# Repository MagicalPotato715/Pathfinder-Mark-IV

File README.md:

# Pathfinder-Mark-IV
**IMPORTANT FOR REVIEWERS**: 
 - 1. The PCB price *really* is at the lowest it could possibly be, it's not possible to lower the price OR try to find a cheaper fab, I already thoroughly went through this with the reviewer @technical_ and he said that it's acceptable.
 - 2. The BOM is already optimized, and NO the parts on Aliexpress and Digikey cannot be sourced from LCSC (technically, LCSC does *sell* the terminal block, but the one seller's out of stock and has been for a while).
 - 3. This is NOT similar to Mk-III in ANY way aside from the fact that it's a hexapod. (if you reviewed it you'd know that) The entire system is completely different. Mk-III was a Nucleo Shield that used a 7.4v lipo battery connected to 3 buck converters directly connected to passives, that was basically it. However, Mk-IV is an on-board, Teensy, with a 6.6v Li-Fe Battery connected to a terminal-rocker switch system, with a back side I2C expander with 8 Tof Sensors.

If you don't believe me, ask @technical_, @NotARoomba, or @Tanook

What: Mark IV will be the fourth generation of my hexapod line: Pathfinder (not to be confused with the Hack Club YSWS). Mark IV will feature major consistency improvements to Mark III (mainly just not featuring buck converters). Additionally, Mark IV has an I2C expander connected to 8 ToF sensors that should allow the finished robot to have some form of autonomous movement.

Note: This project primarily focuses on the PCB of the Mark IV, as the body has already been printed, so it's a secondary focus (however, design tweaks may still be made to it).

Why: I began Pathfinder a year ago after my physics teacher encouraged me to join my school's science fair. I had always had an idea for a spider robot that I kept at the back of my mind, but this pushed me to bring it to life. Over the next few weeks, I poured hours every day into learning more about mechanical and electrical engineering. I also sought mentorship from the UC Berkeley Engineering Department and got connected with a Mech E & EECS graduate student. Mark I of Pathfinder, a simple prototype/proof of concept, was churned out after 2 weeks, just in time for my district's science fair to win me 2nd place. Mark II was developed a few weeks later for the regional science fair, and it featured my very first PCB a simple wire connector that I created using Onboard. Mark III was developed in the months after the science fair. I attempted to create a Hexpod orders of magnitude larger, with a system heavily centered on the PCB (I developed this PCB with Highway). However, when I finally got the PCB, soldered all of the components, and plugged it in, the core of the design: one of 3 buck converters to take 15 amps of power from the 7.4v battery to the 18 servo motors, blew up; ending Mark III. I developed Mark IV to continue on and actualize Pathfinder.

3D Model (Chassis):

3D Model (PCB in Kicad):

PCB Layout:

F. Cu

In1. Cu

In2. Cu

B. Cu

PCB Schematic:

|Name                         |Amount|Unit Cost|Unit Size|Total |FIELD6                                                                                                                                                                                                                                                                                                                                                                                                                                                                                                                                                                                                                                                                                                                                                                                                                                                                    |
|-----------------------------|------|---------|---------|------|--------------------------------------------------------------------------------------------------------------------------------------------------------------------------------------------------------------------------------------------------------------------------------------------------------------------------------------------------------------------------------------------------------------------------------------------------------------------------------------------------------------------------------------------------------------------------------------------------------------------------------------------------------------------------------------------------------------------------------------------------------------------------------------------------------------------------------------------------------------------------|
|3.3v Zener Diode             |1     |0.74     |20       |0.74  |https://www.lcsc.com/product-detail/C7441074.html?s_z=n_1N4728A                                                                                                                                                                                                                                                                                                                                                                                                                                                                                                                                                                                                                                                                                                                                                                                                           |
|SMD Capacitor 10uf 0805      |2     |0.2      |20       |0.2   |https://www.lcsc.com/product-detail/C15850.html?s_z=n_SMD%2520Capacitor%25200805%252010uf                                                                                                                                                                                                                                                                                                                                                                                                                                                                                                                                                                                                                                                                                                                                                                                 |
|Header 1x3 M                 |18    |0.81     |20       |0.81  |https://www.lcsc.com/product-detail/C2937625.html?s_z=n_2.54mm%2520header                                                                                                                                                                                                                                                                                                                                                                                                                                                                                                                                                                                                                                                                                                                                                                                                 |
|Header 1x5 F                 |9     |0.58     |20       |0.58  |https://www.lcsc.com/product-detail/C492404.html?s_z=n_2.54mm                                                                                                                                                                                                                                                                                                                                                                                                                                                                                                                                                                                                                                                                                                                                                                                                             |
|SMD LED                      |20    |0.48     |50       |0.48  |https://www.lcsc.com/product-detail/C25170728.html                                                                                                                                                                                                                                                                                                                                                                                                                                                                                                                                                                                                                                                                                                                                                                                                                        |
|SMD Resistor 510ohm 0805     |19    |0.43     |50       |0.43  |https://www.lcsc.com/product-detail/C2828857.html?s_z=n_0805%2520LED                                                                                                                                                                                                                                                                                                                                                                                                                                                                                                                                                                                                                                                                                                                                                                                                      |
|Servo Motors                 |6     |35.26    |4        |70.52 |https://www.aliexpress.us/item/3256806709778108.html?spm=a2g0o.productlist.0.0.6ab56e340EHKOL&mp=1&pdp_npi=5%40dis%21USD%21USD%20130.38%21USD%2036.58%21%21USD%2036.58%21%21%21%402101062a17638804388948845ec99e%2112000038822514200%21ct%21US%216187826129%21%215%210&_gl=1*cljtcb*_gcl_aw*R0NMLjE3NjM4ODA2ODUuQ2p3S0NBaUEyNFhKQmhCWEVpd0FYRWxPM3liRHZJN1I1VnFod2RBbzJuRGJ3RkJwVWkxX3hRbkJBY2NBVHdfak5hWElKU20wNVJjNTJCb0NjTndRQXZEX0J3RQ..*_gcl_dc*R0NMLjE3NjM4ODA2ODUuQ2p3S0NBaUEyNFhKQmhCWEVpd0FYRWxPM3liRHZJN1I1VnFod2RBbzJuRGJ3RkJwVWkxX3hRbkJBY2NBVHdfak5hWElKU20wNVJjNTJCb0NjTndRQXZEX0J3RQ..*_gcl_au*MTUyNzUyMDgzOS4xNzU3ODgxNTQ1*_ga*MjEzNTUyNTk1My4xNzYzODc4NzU4*_ga_VED1YSGNC7*czE3NjM4Nzg3NTckbzEkZzEkdDE3NjM4ODA5MzQkajYwJGwwJGgw&gatewayAdapt=glo2usa                                                                                                      |
|Li-Fe Battery 6.6v 3000mah   |2     |19.32    |1        |38.64 |https://www.aliexpress.us/item/3256807464251198.html?src=google&pdp_npi=4%40dis%21USD%2111.90%218.33%21%21%21%21%21%40%2112000041655129505%21ppc%21%21%21&src=google&albch=shopping&acnt=231-612-1468&isdl=y&slnk=&plac=&mtctp=&albbt=Google_7_shopping&aff_platform=google&aff_short_key=_oFgTQeV&gclsrc=aw.ds&albagn=888888&ds_e_adid=&ds_e_matchtype=&ds_e_device=c&ds_e_network=x&ds_e_product_group_id=&ds_e_product_id=en3256807464251198&ds_e_product_merchant_id=101200748&ds_e_product_country=US&ds_e_product_language=en&ds_e_product_channel=online&ds_e_product_store_id=&ds_url_v=2&albcp=22977867118&albag=&isSmbAutoCall=false&needSmbHouyi=false&gad_source=1&gad_campaignid=22973747411&gbraid=0AAAABBR8kP1DsTtj-qFVjDN4WDyziy5WL&gclid=CjwKCAiA24XJBhBXEiwAXElO3ybDvI7R5VqhwdAo2nDbwFBpUi1_xQnBAccATw_jNaXIJSm05Rc52BoCcNwQAvD_BwE&gatewayAdapt=glo2usa|
|T-Plug M                     |2     |1.67     |1        |3.34  |https://www.aliexpress.us/item/3256806654144826.html?spm=a2g0o.productlist.main.49.1f564137Zumm2e&algo_pvid=f02dfe0a-6ee5-49a2-bcfe-484b81d72b31&algo_exp_id=f02dfe0a-6ee5-49a2-bcfe-484b81d72b31-48&pdp_ext_f=%7B%22order%22%3A%22664%22%2C%22eval%22%3A%221%22%2C%22fromPage%22%3A%22search%22%7D&pdp_npi=6%40dis%21USD%211.67%211.66%21%21%2111.83%2111.76%21%402101584917638809771278651e3f6e%2112000038478342073%21sea%21US%216187826129%21X%211%210%21n_tag%3A-29919%3Bd%3Ad9d669af%3Bm03_new_user%3A-29895%3BpisId%3A5000000193062241&curPageLogUid=EVB9s7sE3451&utparam-url=scene%3Asearch%7Cquery_from%3A%7Cx_object_id%3A1005006840459578%7C_p_origin_prod%3A                                                                                                                                                                                                   |
|Metal Horn                   |18    |9.99     |15       |19.98 |https://www.amazon.com/Comimark-15Pcs-Metal-Disc-Arm25T-MG996R-RoWTUS/dp/B0855Q36Q3                                                                                                                                                                                                                                                                                                                                                                                                                                                                                                                                                                                                                                                                                                                                                                                       |
|Buck Converter               |1     |9.59     |5        |9.59  |https://www.amazon.com/dp/B0B779ZYN1?ref=cm_sw_r_cp_ud_dp_THWM20P2KPCV3FR988YE&ref_=cm_sw_r_cp_ud_dp_THWM20P2KPCV3FR988YE&social_share=cm_sw_r_cp_ud_dp_THWM20P2KPCV3FR988YE&th=1                                                                                                                                                                                                                                                                                                                                                                                                                                                                                                                                                                                                                                                                                         |
|Terminal Block               |2     |0.78     |1        |1.56  |https://www.digikey.com/en/products/detail/same-sky-formerly-cui-devices/TB005-762-02BE/10064113                                                                                                                                                                                                                                                                                                                                                                                                                                                                                                                                                                                                                                                                                                                                                                          |
|SMD Capacitor 0.1uf 0603     |3     |0.58     |100      |0.58  |https://www.lcsc.com/product-detail/C48579279.html?s_z=n_capacitor%25200603%2520100nf                                                                                                                                                                                                                                                                                                                                                                                                                                                                                                                                                                                                                                                                                                                                                                                     |
|THT Resistor 5k              |1     |2.42     |100      |2.42  |https://www.aliexpress.us/item/3256806020720362.html?spm=a2g0o.productlist.main.21.511d6fc0aABpt6&algo_pvid=170e0595-05cd-41a7-8c4e-a023f098c51a&algo_exp_id=170e0595-05cd-41a7-8c4e-a023f098c51a-20&pdp_ext_f=%7B%22order%22%3A%22209%22%2C%22eval%22%3A%221%22%2C%22fromPage%22%3A%22search%22%7D&pdp_npi=6%40dis%21USD%212.29%211.49%21%21%2116.20%2110.53%21%40214100f417638814026455015e8b9c%2112000036279816949%21sea%21US%216187826129%21X%211%210%21n_tag%3A-29919%3Bd%3Ad9d669af%3Bm03_new_user%3A-29895&curPageLogUid=rHKmPIu0xe2u&utparam-url=scene%3Asearch%7Cquery_from%3A%7Cx_object_id%3A1005006207035114%7C_p_origin_prod%3A                                                                                                                                                                                                                              |
|THT Resistor 4.7k            |2     |2.37     |100      |2.37  |https://www.aliexpress.us/item/3256806020720362.html?spm=a2g0o.cart.0.0.245038da7d89yo&mp=1&pdp_npi=5%40dis%21USD%21USD%202.37%21USD%201.54%21%21USD%201.54%21%21%21%40212a70c117638818440935660eb116%2112000036279816941%21ct%21US%216187826129%21%211%210&_gl=1*mi39am*_gcl_aw*R0NMLjE3NjM4ODA2ODUuQ2p3S0NBaUEyNFhKQmhCWEVpd0FYRWxPM3liRHZJN1I1VnFod2RBbzJuRGJ3RkJwVWkxX3hRbkJBY2NBVHdfak5hWElKU20wNVJjNTJCb0NjTndRQXZEX0J3RQ..*_gcl_dc*R0NMLjE3NjM4ODA2ODUuQ2p3S0NBaUEyNFhKQmhCWEVpd0FYRWxPM3liRHZJN1I1VnFod2RBbzJuRGJ3RkJwVWkxX3hRbkJBY2NBVHdfak5hWElKU20wNVJjNTJCb0NjTndRQXZEX0J3RQ..*_gcl_au*MTUyNzUyMDgzOS4xNzU3ODgxNTQ1*_ga*MjEzNTUyNTk1My4xNzYzODc4NzU4*_ga_VED1YSGNC7*czE3NjM4Nzg3NTckbzEkZzEkdDE3NjM4ODE4NDQkajU5JGwwJGgw&gatewayAdapt=glo2usa                                                                                                                 |
|Electrolytic Capacitor 1500uf|2     |0.6      |5        |0.6   |https://www.lcsc.com/product-detail/C233123.html?s_z=n_capacitor%25200603%2520100nf                                                                                                                                                                                                                                                                                                                                                                                                                                                                                                                                                                                                                                                                                                                                                                                       |
|Teensy 4.1                   |1     |29.6     |1        |29.6  |https://www.digikey.com/en/products/detail/sparkfun-electronics/20359/16688101                                                                                                                                                                                                                                                                                                                                                                                                                                                                                                                                                                                                                                                                                                                                                                                            |
|nRF24L01                     |1     |5.19     |5        |5.19  |https://www.aliexpress.us/item/3256807013648418.html?spm=a2g0o.productlist.main.4.22be30f755mkma&aem_p4p_detail=2025112314271716169132175574500003944458&algo_pvid=ea3e6de3-da62-481e-b087-0651f71a96b7&algo_exp_id=ea3e6de3-da62-481e-b087-0651f71a96b7-3&pdp_ext_f=%7B%22order%22%3A%2248%22%2C%22eval%22%3A%221%22%2C%22fromPage%22%3A%22search%22%7D&pdp_npi=6%40dis%21USD%213.44%213.22%21%21%2124.37%2122.83%21%402101246417639368378132542ef17e%2112000049085881822%21sea%21US%216187826129%21X%211%210%21n_tag%3A-29919%3Bd%3Ad9d669af%3Bm03_new_user%3A-29895&curPageLogUid=apRSrJnZnsNr&utparam-url=scene%3Asearch%7Cquery_from%3A%7Cx_object_id%3A1005007199963170%7C_p_origin_prod%3A&search_p4p_id=2025112314271716169132175574500003944458_1                                                                                                                |
|PCA9548ADB                   |1     |1.38     |1        |1.38  |https://www.lcsc.com/product-detail/C2860563.html?s_z=n_PCA9548ADB                                                                                                                                                                                                                                                                                                                                                                                                                                                                                                                                                                                                                                                                                                                                                                                                        |
|SMD Resistor 10k 0805        |18    |0.19     |100      |0.19  |https://www.aliexpress.us/item/3256804579227354.html?spm=a2g0o.productlist.main.3.60106cf0fgaBdG&algo_pvid=d75aea1c-7e41-4d40-ae2a-47ae5658f480&algo_exp_id=d75aea1c-7e41-4d40-ae2a-47ae5658f480-2&pdp_ext_f=%7B%22order%22%3A%2240%22%2C%22eval%22%3A%221%22%2C%22fromPage%22%3A%22search%22%7D&pdp_npi=6%40dis%21USD%211.10%211.02%21%21%211.10%211.02%21%402140c1e917638798918441521ec5ce%2112000030388976233%21sea%21US%216187826129%21X%211%210%21n_tag%3A-29919%3Bd%3Ad9d669af%3Bm03_new_user%3A-29895&curPageLogUid=uxIWY6qmpv79&utparam-url=scene%3Asearch%7Cquery_from%3A%7Cx_object_id%3A1005004765542106%7C_p_origin_prod%3A                                                                                                                                                                                                                                   |
|BNO055                       |1     |26.9     |1        |26.9  |https://www.aliexpress.us/item/3256809169239048.html?gatewayAdapt=glo2usa                                                                                                                                                                                                                                                                                                                                                                                                                                                                                                                                                                                                                                                                                                                                                                                                 |
|Rocker Switch                |1     |7.39     |12       |7.39  |https://www.aliexpress.us/item/3256806293672719.html?spm=a2g0o.productlist.main.2.78a0644atD9quO&algo_pvid=3815a642-0954-4f1c-a4af-61413e386dff&algo_exp_id=3815a642-0954-4f1c-a4af-61413e386dff-1&pdp_ext_f=%7B%22order%22%3A%2222%22%2C%22eval%22%3A%221%22%2C%22fromPage%22%3A%22search%22%7D&pdp_npi=6%40dis%21USD%217.39%214.29%21%21%2152.32%2130.35%21%40213ba8cc17639376988783322ead26%2112000037354442242%21sea%21US%216187826129%21X%211%210%21n_tag%3A-29919%3Bd%3Ad9d669af%3Bm03_new_user%3A-29895&curPageLogUid=iWplsi7s8ylp&utparam-url=scene%3Asearch%7Cquery_from%3A%7Cx_object_id%3A1005006479987471%7C_p_origin_prod%3A                                                                                                                                                                                                                                 |
|JLCPCB                       |1     |74.42    |5        |74.42 |                                                                                                                                                                                                                                                                                                                                                                                                                                                                                                                                                                                                                                                                                                                                                                                                                                                                          |
|Price Without Taxes/Shipping                             |      |         |Total =  |297.91|                                                                                                                                                                                                                                                                                                                                                                                                                                                                                                                                                                                                                                                                                                                                                                                                                                                                          |

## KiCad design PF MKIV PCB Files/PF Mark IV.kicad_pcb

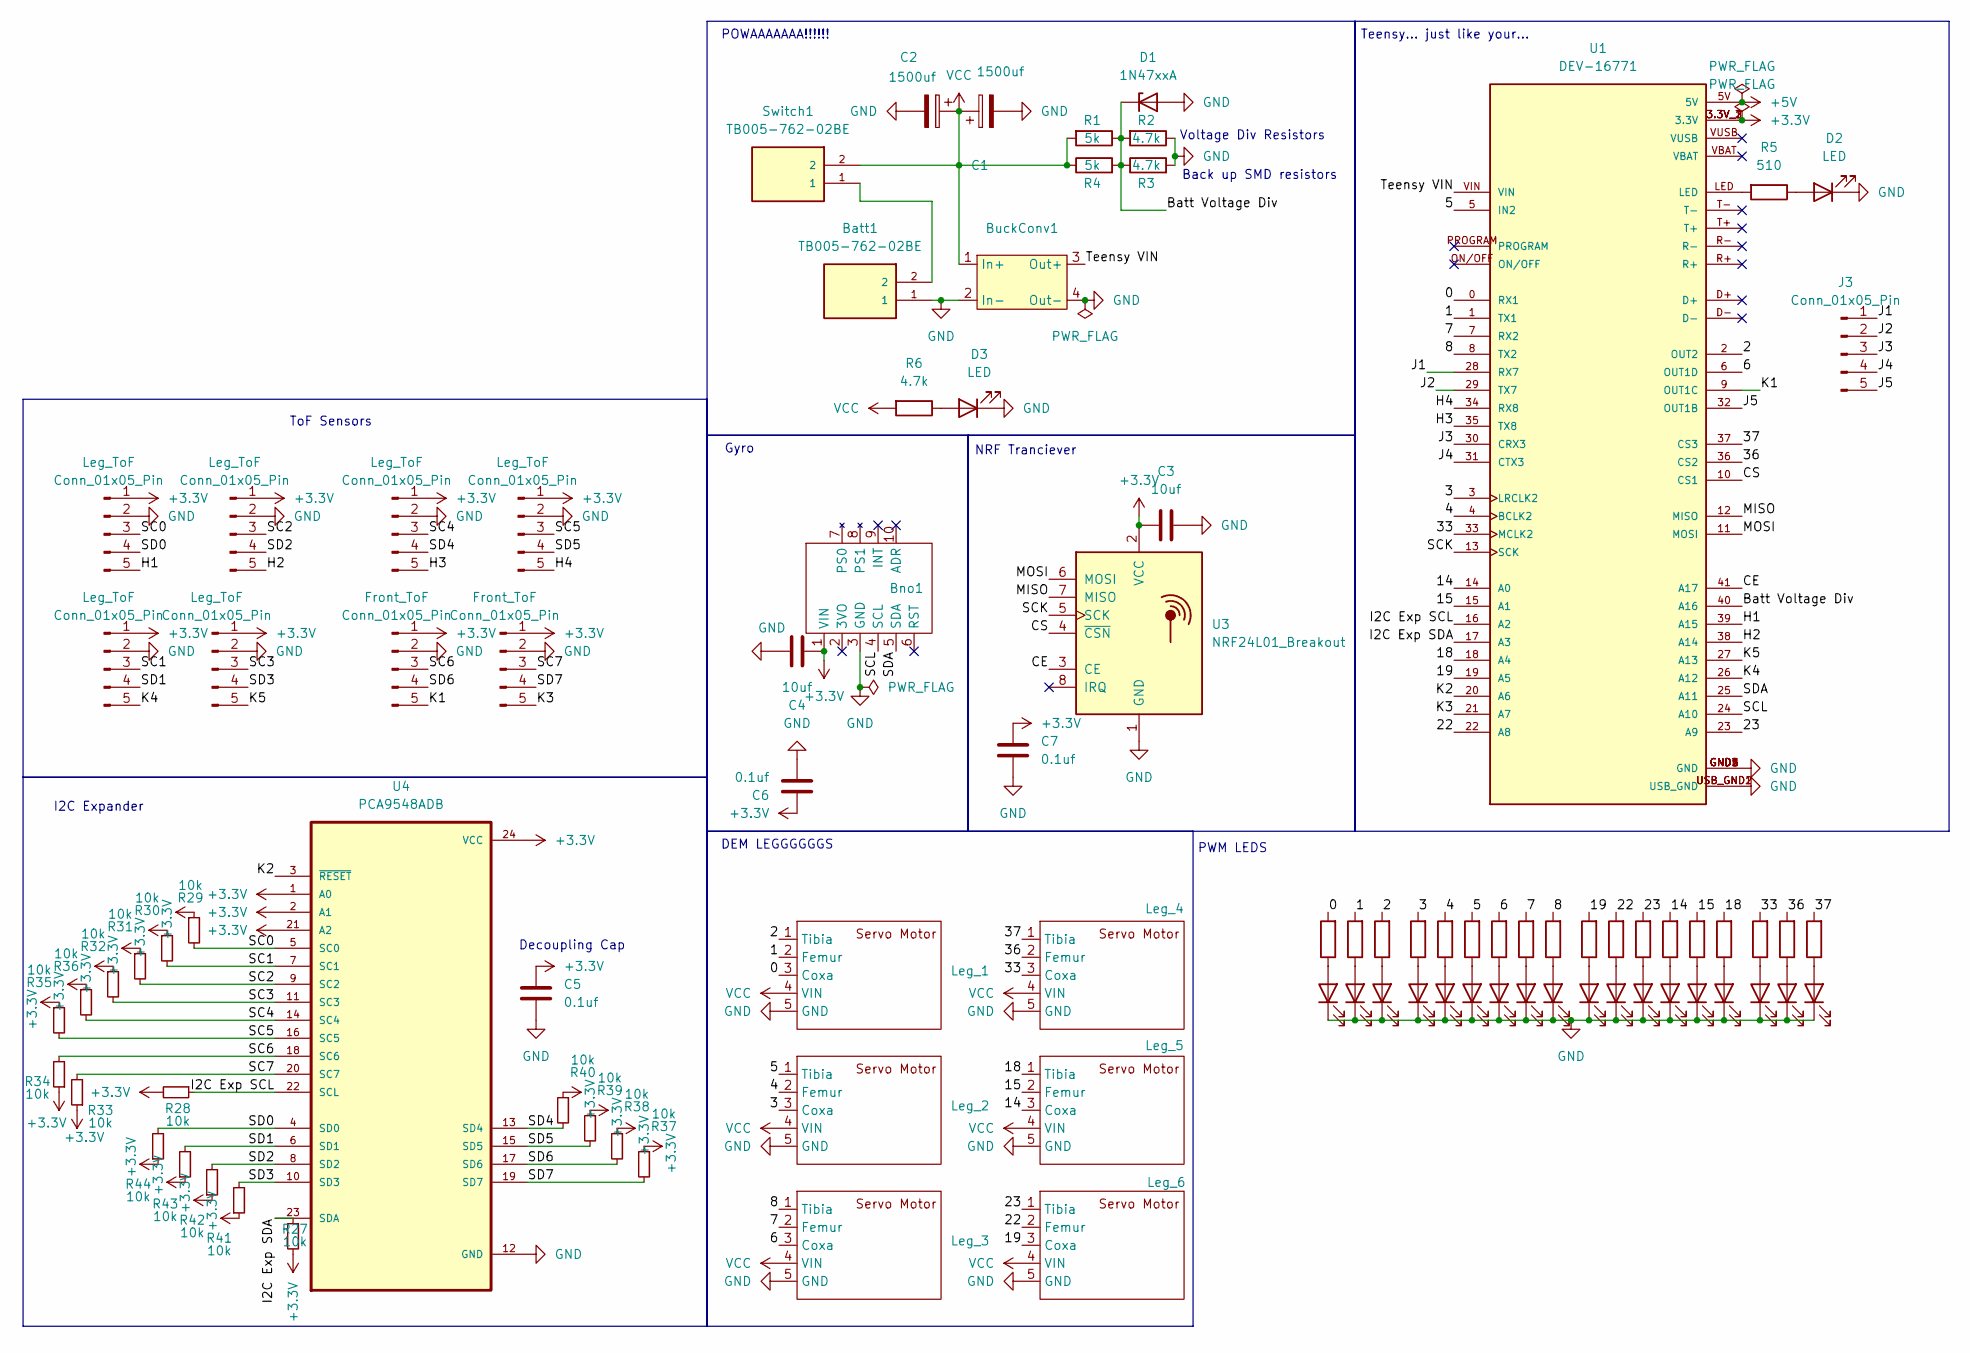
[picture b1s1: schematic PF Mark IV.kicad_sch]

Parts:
Batt1: TB005-762-02BE; CUI_TB005-762-02BE
Bno1: BNO055
BuckConv1: Buck Converter 5V MP1584EN
C1, C2: 1500uf; CP_Radial_D10.0mm_P5.00mm
C3, C4: 10uf; C_0805_2012Metric_Pad1.18x1.45mm_HandSolder
C5, C6, C7: 0.1uf; C_0603_1608Metric_Pad1.08x0.95mm_HandSolder
D1: 1N47xxA; D_DO-41_SOD81_P10.16mm_Horizontal
D2, D3, D4, D5, D6, D7, D8, D9, D10, D11, D12, D13, D14, D15, D16, D17, D18, D19, D20, D21: LED; LED_0805_2012Metric_Pad1.15x1.40mm_HandSolder
Front_ToF: Conn_01x05_Pin; PinHeader_1x05_P2.54mm_Vertical
J3: Conn_01x05_Pin; PinHeader_1x05_P2.54mm_Vertical
Leg_1, Leg_2, Leg_3, Leg_4, Leg_5, Leg_6: Leg_Servo
Leg_ToF: Conn_01x05_Pin; PinHeader_1x05_P2.54mm_Vertical
R1: 5k; R_Axial_DIN0207_L6.3mm_D2.5mm_P10.16mm_Horizontal
R2, R6: 4.7k; R_Axial_DIN0207_L6.3mm_D2.5mm_P10.16mm_Horizontal
R3: 4.7k; R_0805_2012Metric_Pad1.20x1.40mm_HandSolder
R4: 5k; R_0805_2012Metric_Pad1.20x1.40mm_HandSolder
R5, R7, R8, R9, R10, R11, R12, R13, R14, R15, R16, R17, R18, R19, R20, R21, R22, R23, R24: 510; R_0805_2012Metric_Pad1.20x1.40mm_HandSolder
R27, R28, R29, R30, R31, R32, R33, R34, R35, R36, R37, R38, R39, R40, R41, R42, R43, R44: 10k; R_0805_2012Metric_Pad1.20x1.40mm_HandSolder
Switch1: TB005-762-02BE; CUI_TB005-762-02BE
U1: DEV-16771; MODULE_DEV-16771; PARTREV 4.1
U3: NRF24L01_Breakout; nRF24L01_Breakout
U4: PCA9548ADB; SOP65P780X200-24N

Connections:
+3.3V: Bno1.1 (VIN), C3.1, C4.1, C5.1, C6.1, C7.1, Front_ToF.1, Leg_ToF.1, R27.2, R28.2, R29.1, R30.1, R31.1, R32.1, R33.1, R34.1, R35.1, R36.1, R37.1, R38.1, R39.1, R40.1, R41.1, R42.1, R43.1, R44.1, U1.3.3V_1 (3.3V), U1.3.3V_2 (3.3V), U1.3.3V_3 (3.3V), U3.2 (VCC), U4.1 (A0), U4.2 (A1), U4.21 (A2), U4.24 (VCC); also elsewhere on the board
+5V: U1.5V
/0: Leg_1.3 (Coxa), R24.2, U1.0 (RX1)
/1: Leg_1.2 (Femur), R23.2, U1.1 (TX1)
/2: Leg_1.1 (Tibia), R22.2, U1.2 (OUT2)
/3: Leg_2.3 (Coxa), R21.2, U1.3 (LRCLK2)
/4: Leg_2.2 (Femur), R20.2, U1.4 (BCLK2)
/5: Leg_2.1 (Tibia), R19.2, U1.5 (IN2)
/6: Leg_3.3 (Coxa), R18.2, U1.6 (OUT1D)
/7: Leg_3.2 (Femur), R17.2, U1.7 (RX2)
/8: Leg_3.1 (Tibia), R16.2, U1.8 (TX2)
/14: Leg_5.3 (Coxa), R12.2, U1.14 (A0)
/15: Leg_5.2 (Femur), R11.2, U1.15 (A1)
/18: Leg_5.1 (Tibia), R10.2, U1.18 (A4)
/19: Leg_6.3 (Coxa), R15.2, U1.19 (A5)
/22: Leg_6.2 (Femur), R14.2, U1.22 (A8)
/23: Leg_6.1 (Tibia), R13.2, U1.23 (A9)
/33: Leg_4.3 (Coxa), R9.2, U1.33 (MCLK2)
/36: Leg_4.2 (Femur), R8.2, U1.36 (CS2)
/37: Leg_4.1 (Tibia), R7.2, U1.37 (CS3)
/Batt Voltage Div: D1.1 (K), R1.1, R2.2, R3.1, R4.2, U1.40 (A16)
/CE: U1.41 (A17), U3.3 (CE)
/CS: U1.10 (CS1), U3.4 (~CSN)
/H1: Leg_ToF.5, U1.39 (A15); also elsewhere on the board
/H2: Leg_ToF.5, U1.38 (A14); also elsewhere on the board
/H3: Leg_ToF.5, U1.35 (TX8); also elsewhere on the board
/H4: Leg_ToF.5, U1.34 (RX8); also elsewhere on the board
/I2C Exp SCL: R28.1, U1.16 (A2), U4.22 (SCL)
/I2C Exp SDA: R27.1, U1.17 (A3), U4.23 (SDA)
/J1: J3.1, U1.28 (RX7)
/J2: J3.2, U1.29 (TX7)
/J3: J3.3, U1.30 (CRX3)
/J4: J3.4, U1.31 (CTX3)
/J5: J3.5, U1.32 (OUT1B)
/K1: Front_ToF.5, U1.9 (OUT1C); also elsewhere on the board
/K2: U1.20 (A6), U4.3 (~RESET)
/K3: Front_ToF.5, U1.21 (A7); also elsewhere on the board
/K4: Leg_ToF.5, U1.26 (A12); also elsewhere on the board
/K5: Leg_ToF.5, U1.27 (A13); also elsewhere on the board
/MISO: U1.12 (MISO), U3.7 (MISO)
/MOSI: U1.11 (MOSI), U3.6 (MOSI)
/SC0: Leg_ToF.3, R29.2, U4.5 (SC0); also elsewhere on the board
/SC1: Leg_ToF.3, R30.2, U4.7 (SC1); also elsewhere on the board
/SC2: Leg_ToF.3, R31.2, U4.9 (SC2); also elsewhere on the board
/SC3: Leg_ToF.3, R32.2, U4.11 (SC3); also elsewhere on the board
/SC4: Leg_ToF.3, R36.2, U4.14 (SC4); also elsewhere on the board
/SC5: Leg_ToF.3, R35.2, U4.16 (SC5); also elsewhere on the board
/SC6: Front_ToF.3, R34.2, U4.18 (SC6); also elsewhere on the board
/SC7: Front_ToF.3, R33.2, U4.20 (SC7); also elsewhere on the board
/SCK: U1.13 (SCK), U3.5 (SCK)
/SCL: Bno1.4 (SCL), U1.24 (A10)
/SD0: Leg_ToF.4, R44.2, U4.4 (SD0); also elsewhere on the board
/SD1: Leg_ToF.4, R43.2, U4.6 (SD1); also elsewhere on the board
/SD2: Leg_ToF.4, R42.2, U4.8 (SD2); also elsewhere on the board
/SD3: Leg_ToF.4, R41.2, U4.10 (SD3); also elsewhere on the board
/SD4: Leg_ToF.4, R40.2, U4.13 (SD4); also elsewhere on the board
/SD5: Leg_ToF.4, R39.2, U4.15 (SD5); also elsewhere on the board
/SD6: Front_ToF.4, R38.2, U4.17 (SD6); also elsewhere on the board
/SD7: Front_ToF.4, R37.2, U4.19 (SD7); also elsewhere on the board
/SDA: Bno1.5 (SDA), U1.25 (A11)
/Teensy VIN: BuckConv1.3 (Out+), U1.VIN
GND: Batt1.1, Bno1.3 (GND), BuckConv1.2 (In-), BuckConv1.4 (Out-), C1.2, C2.2, C3.2, C4.2, C5.2, C6.2, C7.2, D1.2 (A), D2.1 (K), D3.1 (K), D4.1 (K), D5.1 (K), D6.1 (K), D7.1 (K), D8.1 (K), D9.1 (K), D10.1 (K), D11.1 (K), D12.1 (K), D13.1 (K), D14.1 (K), D15.1 (K), D16.1 (K), D17.1 (K), D18.1 (K), D19.1 (K), D20.1 (K), D21.1 (K), Front_ToF.2, Leg_1.5 (GND), Leg_2.5 (GND), Leg_3.5 (GND), Leg_4.5 (GND), Leg_5.5 (GND), Leg_6.5 (GND), Leg_ToF.2, R2.1, R3.2, U1.GND1 (GND), U1.GND2 (GND), U1.GND3 (GND), U1.GND4 (GND), U1.GND5 (GND), U1.USB_GND1 (USB_GND), U1.USB_GND2 (USB_GND), U3.1 (GND), U4.12 (GND); also elsewhere on the board
unnamed: Batt1.2, Switch1.1
unnamed: D2.2 (A), R5.1
unnamed: D3.2 (A), R6.1
unnamed: D4.2 (A), R7.1
unnamed: D5.2 (A), R8.1
unnamed: D6.2 (A), R9.1
unnamed: D7.2 (A), R10.1
unnamed: D8.2 (A), R11.1
unnamed: D9.2 (A), R12.1
unnamed: D10.2 (A), R13.1
unnamed: D11.2 (A), R14.1
unnamed: D12.2 (A), R15.1
unnamed: D13.2 (A), R16.1
unnamed: D14.2 (A), R17.1
unnamed: D15.2 (A), R18.1
unnamed: D16.2 (A), R19.1
unnamed: D17.2 (A), R20.1
unnamed: D18.2 (A), R21.1
unnamed: D19.2 (A), R22.1
unnamed: D20.2 (A), R23.1
unnamed: D21.2 (A), R24.1
unnamed: R5.2, U1.LED
VCC: BuckConv1.1 (In+), C1.1, C2.1, Leg_1.4 (VIN), Leg_2.4 (VIN), Leg_3.4 (VIN), Leg_4.4 (VIN), Leg_5.4 (VIN), Leg_6.4 (VIN), R1.2, R4.1, R6.2, Switch1.2

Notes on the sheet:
NRF Tranciever
DEM LEGGGGGGS
PWM LEDS
Gyro
Teensy... just like your...
Voltage Div Resistors
Decoupling Cap
I2C Expander
ToF Sensors
Back up SMD resistors
POWAAAAAAA!!!!!!

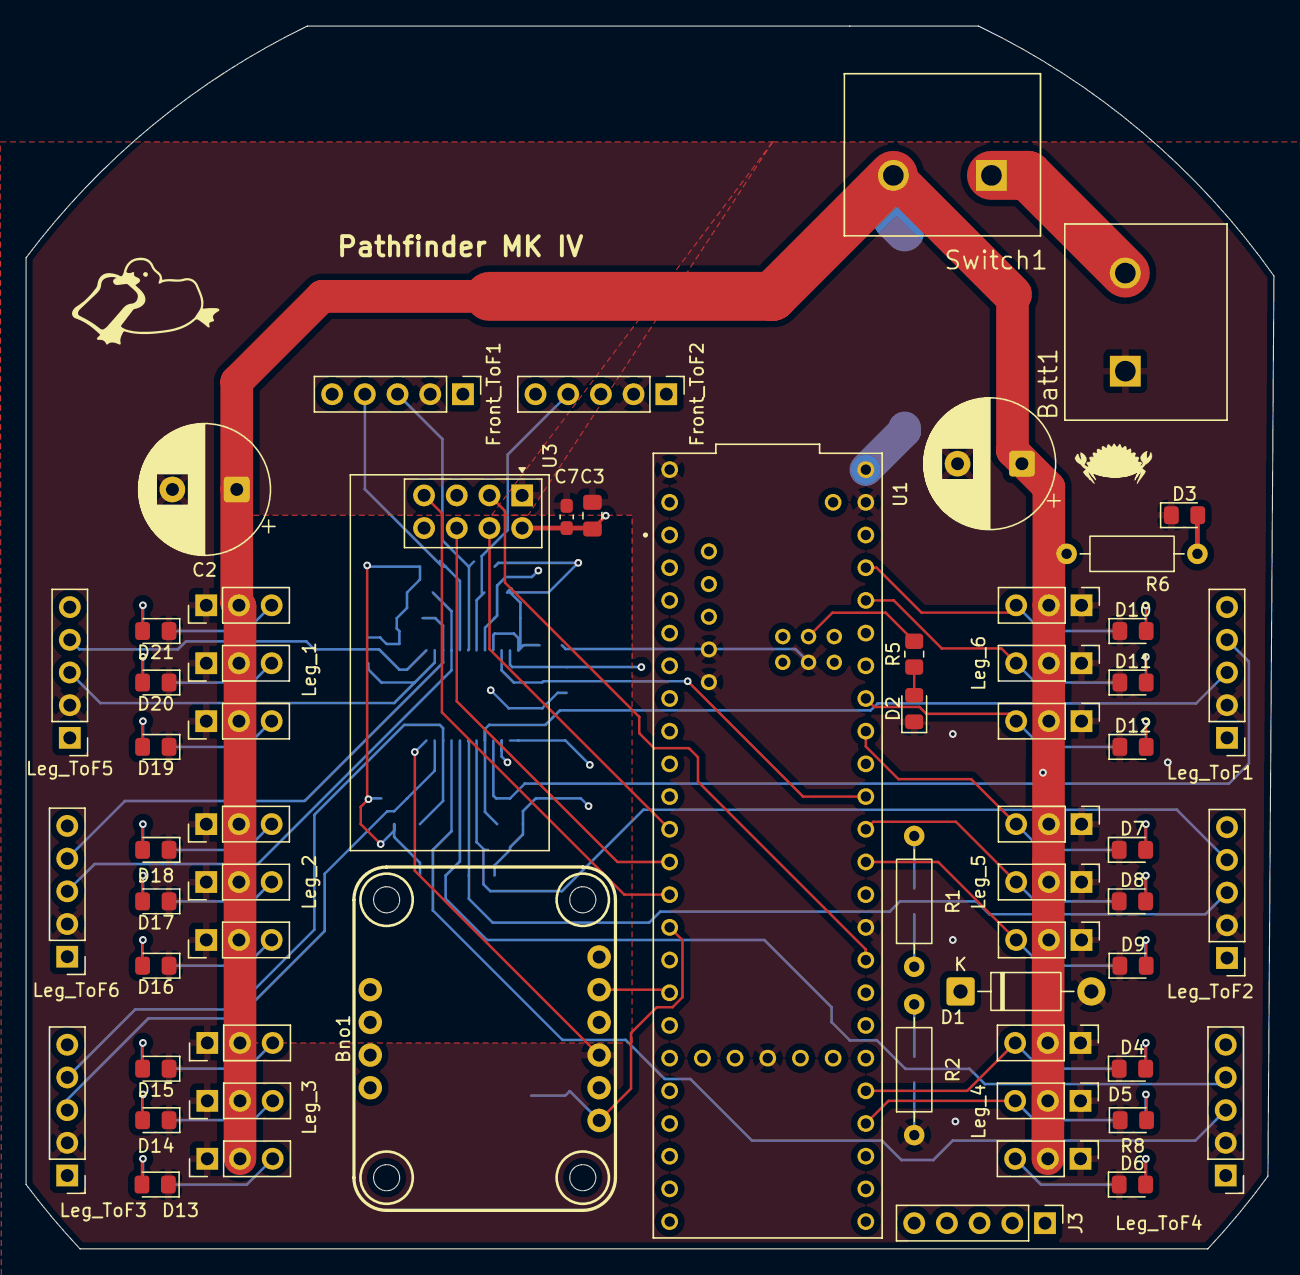
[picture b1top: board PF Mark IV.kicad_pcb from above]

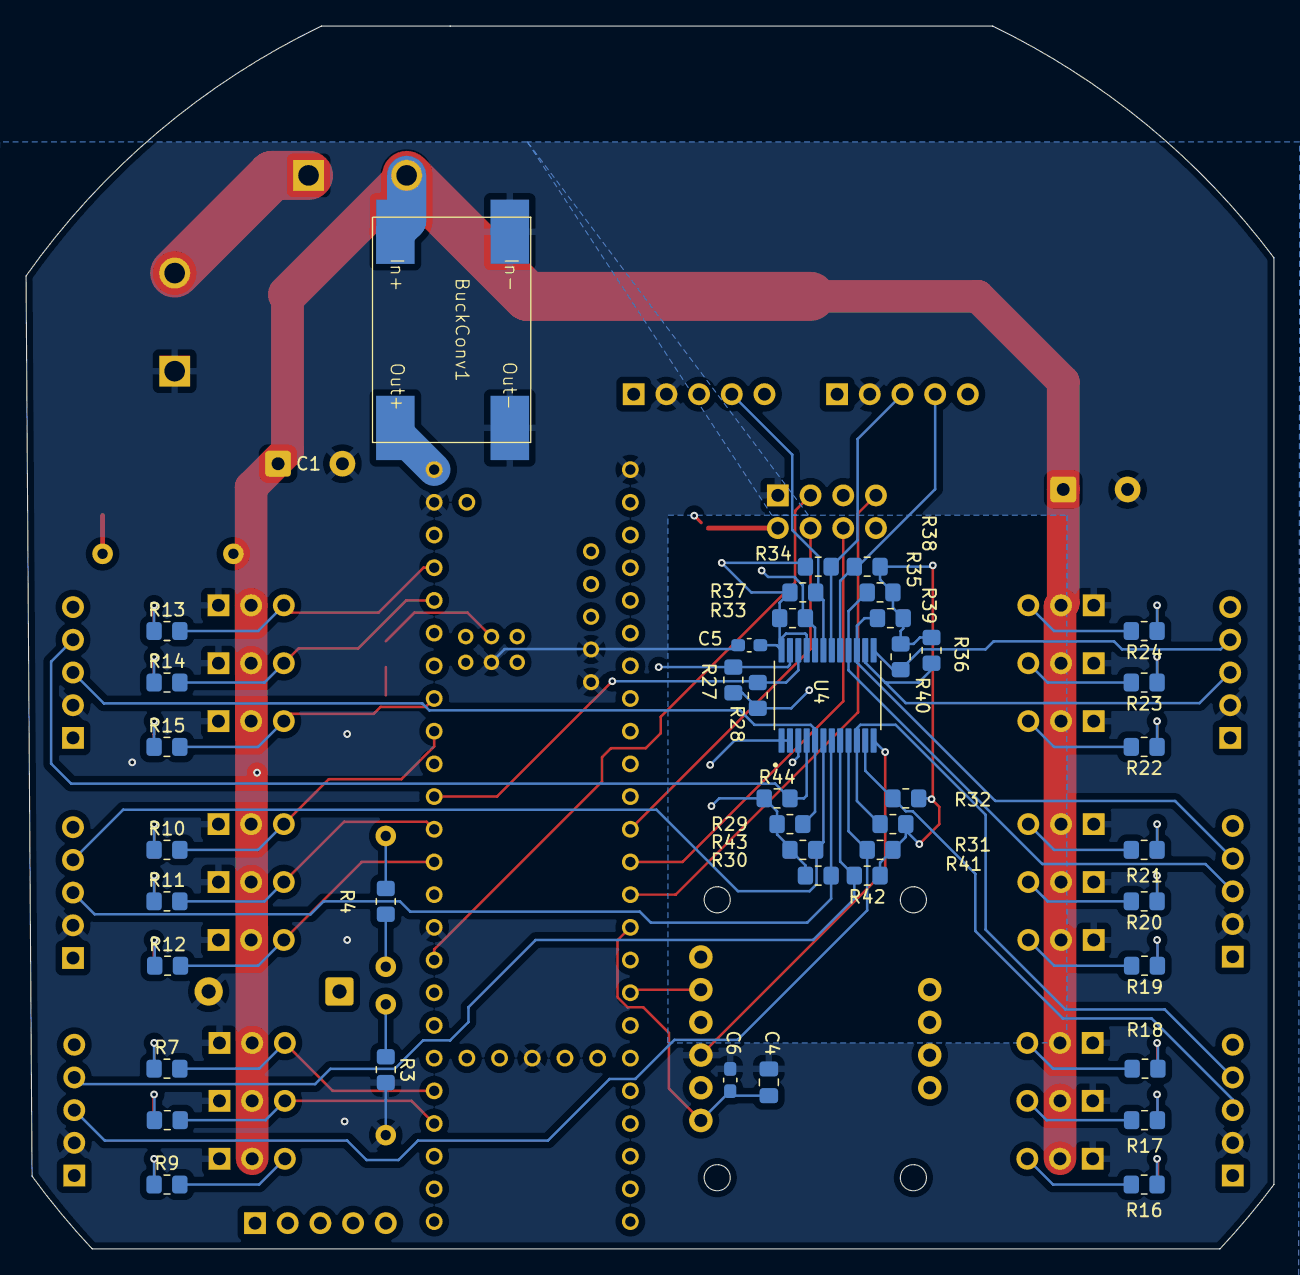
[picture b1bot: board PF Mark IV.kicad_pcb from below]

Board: 4 copper layers, 96.9 x 95.0 mm, 92 parts (43 on the bottom side), 84 nets.

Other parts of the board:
Front_ToF1, Front_ToF2: Conn_01x05_Pin; PinHeader_1x05_P2.54mm_Vertical
Leg_ToF1, Leg_ToF2, Leg_ToF3, Leg_ToF4, Leg_ToF5, Leg_ToF6: Conn_01x05_Pin; PinHeader_1x05_P2.54mm_Vertical

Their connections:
+3.3V: Front_ToF1.1, Front_ToF2.1, Leg_ToF1.1, Leg_ToF2.1, Leg_ToF3.1, Leg_ToF4.1, Leg_ToF5.1, Leg_ToF6.1; also elsewhere on the board
/H1: Leg_ToF1.5; also elsewhere on the board
/H2: Leg_ToF4.5; also elsewhere on the board
/H3: Leg_ToF5.5; also elsewhere on the board
/H4: Leg_ToF6.5; also elsewhere on the board
/K1: Front_ToF1.5; also elsewhere on the board
/K3: Front_ToF2.5; also elsewhere on the board
/K4: Leg_ToF2.5; also elsewhere on the board
/K5: Leg_ToF3.5; also elsewhere on the board
/SC0: Leg_ToF1.3; also elsewhere on the board
/SC1: Leg_ToF2.3; also elsewhere on the board
/SC2: Leg_ToF4.3; also elsewhere on the board
/SC3: Leg_ToF3.3; also elsewhere on the board
/SC4: Leg_ToF5.3; also elsewhere on the board
/SC5: Leg_ToF6.3; also elsewhere on the board
/SC6: Front_ToF1.3; also elsewhere on the board
/SC7: Front_ToF2.3; also elsewhere on the board
/SD0: Leg_ToF1.4; also elsewhere on the board
/SD1: Leg_ToF2.4; also elsewhere on the board
/SD2: Leg_ToF4.4; also elsewhere on the board
/SD3: Leg_ToF3.4; also elsewhere on the board
/SD4: Leg_ToF5.4; also elsewhere on the board
/SD5: Leg_ToF6.4; also elsewhere on the board
/SD6: Front_ToF1.4; also elsewhere on the board
/SD7: Front_ToF2.4; also elsewhere on the board
GND: Front_ToF1.2, Front_ToF2.2, Leg_ToF1.2, Leg_ToF2.2, Leg_ToF3.2, Leg_ToF4.2, Leg_ToF5.2, Leg_ToF6.2; also elsewhere on the board

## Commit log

2025-11-23 Create Ignore
2025-11-24 Create delete
2025-12-03 Revise component list and links in README
    Updated the component list and their details in the README.
2025-12-05 Update component prices and add totals
2025-12-07 Update README with Mk-IV details and reviewer notes
    Added clarification about differences between Mk-III and Mk-IV, and updated reviewer mentions.
